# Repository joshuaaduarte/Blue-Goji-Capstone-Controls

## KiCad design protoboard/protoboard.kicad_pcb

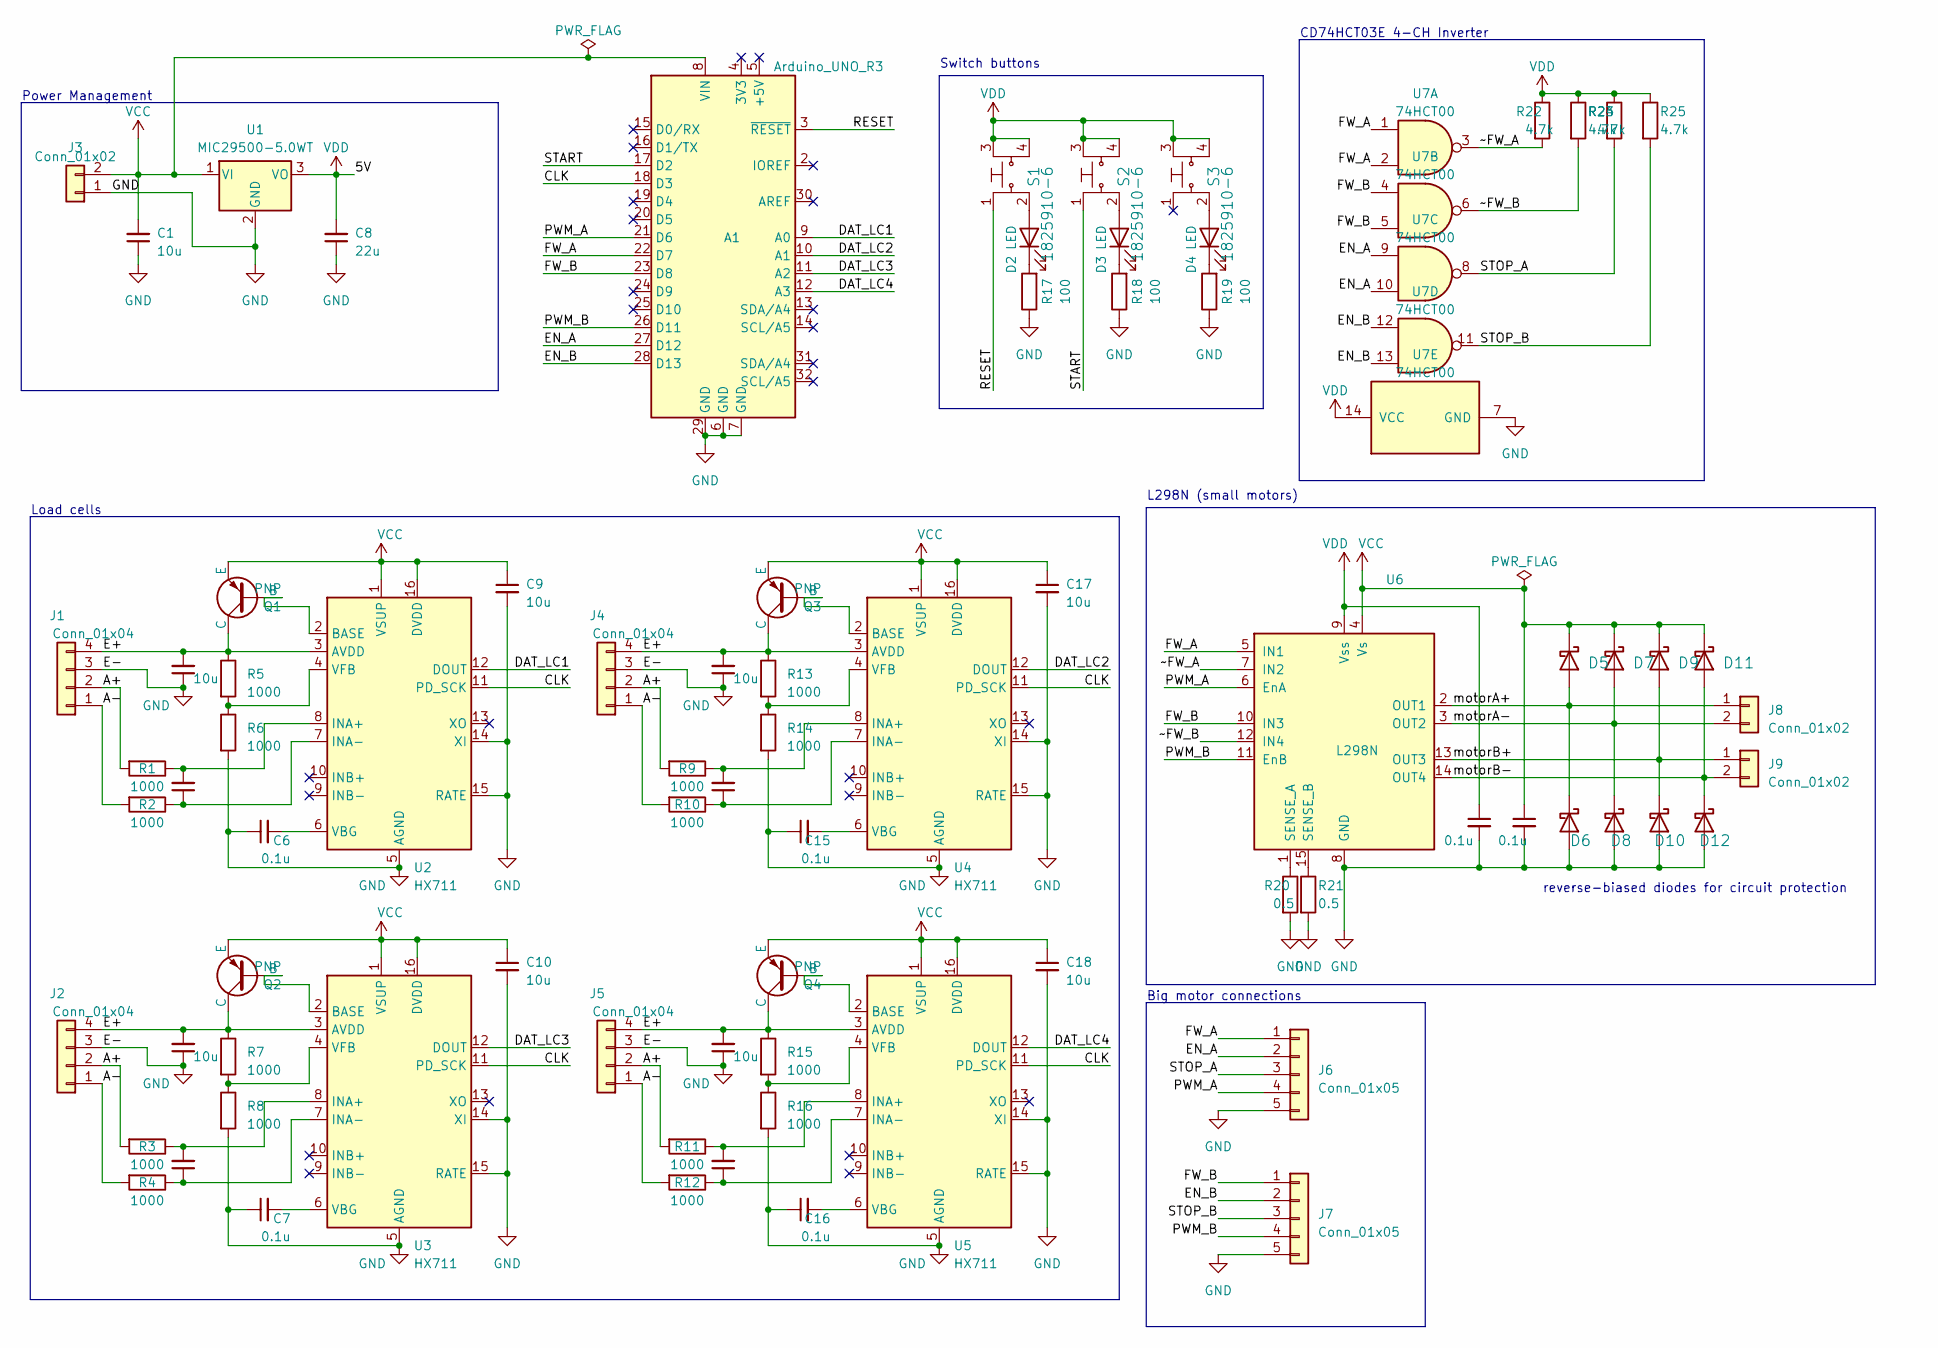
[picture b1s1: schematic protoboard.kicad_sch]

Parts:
A1: Arduino_UNO_R3
C1: 10u; CP_Radial_Tantal_D5.5mm_P2.50mm
C2, C4, C9, C10, C11, C13, C17, C18: 10u; CP_Radial_D5.0mm_P2.50mm
C3, C5, C6, C7, C12, C14, C15, C16: 0.1u; CP_Radial_D5.0mm_P2.50mm
C8: 22u; CP_Radial_Tantal_D5.5mm_P2.50mm
C19, C20: 0.1u; CP_Radial_Tantal_D5.5mm_P2.50mm
D2, D3, D4: LED; LED_D1.8mm_W1.8mm_H2.4mm_Horizontal_O1.27mm_Z1.6mm
D5, D6, D7, D8, D9, D10, D11, D12: 1N5820-TP; D_DO-201AD_P15.24mm_Horizontal; MPN 1N4001-TP; Digi-Key_PN 1N4001-TPMSCT-ND
J1, J2, J4, J5: Conn_01x04; TerminalBlock_bornier-4_P5.08mm
J3, J8, J9: Conn_01x02; TerminalBlock_TE_282834-2_1x02_P2.54mm_Horizontal
J6, J7: Conn_01x05; TerminalBlock_bornier-5_P5.08mm
Q1, Q2, Q3, Q4: PNP; TO-92
R1, R2, R3, R4, R5, R6, R7, R8, R9, R10, R11, R12, R13, R14, R15, R16: 1000; R_Axial_DIN0204_L3.6mm_D1.6mm_P2.54mm_Vertical
R17, R18, R19: 100; R_Axial_DIN0204_L3.6mm_D1.6mm_P2.54mm_Vertical
R20, R21: 0.5; R_Axial_DIN0204_L3.6mm_D1.6mm_P2.54mm_Vertical
R22, R23, R24, R25: 4.7k; R_Axial_DIN0204_L3.6mm_D1.6mm_P2.54mm_Vertical
S1, S2, S3: 1825910-6; Switch_Tactile_THT_6x6mm; MPN 1825910-6; Digi-Key_PN 450-1650-ND
U1: MIC29500-5.0WT; TO-220-3
U2, U3, U4, U5: HX711; SOP-16_3.9x9.9mm_P1.27mm
U6: L298N; TO-220-15_P2.54x2.54mm_StaggerOdd_Lead4.58mm_Vertical
U7: 74HCT00; DIP-14_W7.62mm

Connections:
/A+: J1.2, J2.2, J4.2, J5.2, R1.2, R3.2, R9.2, R11.2
/A-: J1.1, J2.1, J4.1, J5.1, R2.2, R4.2, R10.2, R12.2
/CLK: A1.18 (D3), U2.11 (PD_SCK), U3.11 (PD_SCK), U4.11 (PD_SCK), U5.11 (PD_SCK)
/DAT_LC1: A1.9 (A0), U2.12 (DOUT)
/DAT_LC2: A1.10 (A1), U4.12 (DOUT)
/DAT_LC3: A1.11 (A2), U3.12 (DOUT)
/DAT_LC4: A1.12 (A3), U5.12 (DOUT)
/E+: C2.2, C4.2, C11.2, C13.2, J1.4, J2.4, J4.4, J5.4, Q1.1 (C), Q2.1 (C), Q3.1 (C), Q4.1 (C), R5.1, R7.1, R13.1, R15.1, U2.3 (AVDD), U3.3 (AVDD), U4.3 (AVDD), U5.3 (AVDD)
/EN_A: A1.27 (D12), J6.2, U7.9, U7.10
/EN_B: A1.28 (D13), J7.2, U7.12, U7.13
/FW_A: A1.22 (D7), J6.1, U6.5 (IN1), U7.1, U7.2
/FW_B: A1.23 (D8), J7.1, U6.10 (IN3), U7.4, U7.5
/PWM_A: A1.21 (D6), J6.4, U6.6 (EnA)
/PWM_B: A1.26 (D11), J7.4, U6.11 (EnB)
/RESET: A1.3 (~RESET), S1.1
/START: A1.17 (D2), S2.1
/STOP_A: J6.3, R24.2, U7.8
/STOP_B: J7.3, R25.2, U7.11
/motorA+: D5.2 (A), D6.1 (K), J8.1, U6.2 (OUT1)
/motorA-: D7.2 (A), D8.1 (K), J8.2, U6.3 (OUT2)
/motorB+: D9.2 (A), D10.1 (K), J9.1, U6.13 (OUT3)
/motorB-: D11.2 (A), D12.1 (K), J9.2, U6.14 (OUT4)
/~FW_A: R22.2, U6.7 (IN2), U7.3
/~FW_B: R23.2, U6.12 (IN4), U7.6
GND: A1.6 (GND), A1.7 (GND), A1.29 (GND), C1.1, C2.1, C4.1, C6.1, C7.1, C8.1, C9.2, C10.2, C11.1, C13.1, C15.1, C16.1, C17.2, C18.2, C19.2, C20.2, D6.2 (A), D8.2 (A), D10.2 (A), D12.2 (A), J1.3, J2.3, J3.1, J4.3, J5.3, J6.5, J7.5, R6.2, R8.2, R14.2, R16.2, R17.1, R18.1, R19.1, R20.2, R21.2, U1.2 (GND), U2.5 (AGND), U2.14 (XI), U2.15 (RATE), U3.5 (AGND), U3.14 (XI), U3.15 (RATE), U4.5 (AGND), U4.14 (XI), U4.15 (RATE), U5.5 (AGND), U5.14 (XI), U5.15 (RATE), U6.8 (GND), U7.7 (GND)
unnamed: D2.2 (A), S1.2
unnamed: D2.1 (K), R17.2
unnamed: D3.2 (A), S2.2
unnamed: D3.1 (K), R18.2
unnamed: D4.2 (A), S3.2
unnamed: D4.1 (K), R19.2
unnamed: Q1.2 (B), U2.2 (BASE)
unnamed: Q2.2 (B), U3.2 (BASE)
unnamed: Q3.2 (B), U4.2 (BASE)
unnamed: Q4.2 (B), U5.2 (BASE)
unnamed: C3.2, R1.1, U2.8 (INA+)
unnamed: C3.1, R2.1, U2.7 (INA-)
unnamed: C6.2, U2.6 (VBG)
unnamed: R5.2, R6.1, U2.4 (VFB)
unnamed: C5.2, R3.1, U3.8 (INA+)
unnamed: C5.1, R4.1, U3.7 (INA-)
unnamed: C7.2, U3.6 (VBG)
unnamed: R7.2, R8.1, U3.4 (VFB)
unnamed: C12.2, R9.1, U4.8 (INA+)
unnamed: C12.1, R10.1, U4.7 (INA-)
unnamed: C15.2, U4.6 (VBG)
unnamed: R13.2, R14.1, U4.4 (VFB)
unnamed: C14.2, R11.1, U5.8 (INA+)
unnamed: C14.1, R12.1, U5.7 (INA-)
unnamed: C16.2, U5.6 (VBG)
unnamed: R15.2, R16.1, U5.4 (VFB)
unnamed: R20.1, U6.1 (SENSE_A)
unnamed: R21.1, U6.15 (SENSE_B)
VCC: A1.8 (VIN), C1.2, C9.1, C10.1, C17.1, C18.1, C20.1, D5.1 (K), D7.1 (K), D9.1 (K), D11.1 (K), J3.2, Q1.3 (E), Q2.3 (E), Q3.3 (E), Q4.3 (E), U1.1 (VI), U2.1 (VSUP), U2.16 (DVDD), U3.1 (VSUP), U3.16 (DVDD), U4.1 (VSUP), U4.16 (DVDD), U5.1 (VSUP), U5.16 (DVDD), U6.4 (Vs)
VDD: C8.2, C19.1, R22.1, R23.1, R24.1, R25.1, S1.3, S1.4, S2.3, S2.4, S3.3, S3.4, U1.3 (VO), U6.9 (Vss), U7.14 (VCC)

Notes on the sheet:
CD74HCT03E 4-CH Inverter
Switch buttons
Load cells
reverse-biased diodes for circuit protection
L298N (small motors)
Power Management
Big motor connections

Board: 2 copper layers, 80 parts (0 on the bottom side), 55 nets, no tracks yet.

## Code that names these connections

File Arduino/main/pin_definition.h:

/*
 * Blue Goji Omnidirectional Treadmill Capstone
 * University of California Berkeley MEng 2023
 * Author: Billy Lin 
 * Last-Edit: 02-14-2023
 */

#ifndef PIN_DEFINITION_H
#define PIN_DEFINITION_H

// motor pin definitions
#define pwmA 6
#define pwmB 11
#define fwA 7 // equivalent to in1A, in2A is obtained by negating this signal
#define fwB 8
#define enA 12 // only used in big motors
#define enB 13

// Pin definitions for load cells
#define clk 3
#define dat_lc1 14
#define dat_lc2 15
#define dat_lc3 16
#define dat_lc4 17

#define startButton 2  // Green
#define emergencyButton 4 // Yellow

#endif

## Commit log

2022-12-07 Initial commit with pose function
2023-01-20 Updated script to include center point on hip and arrow that will change with direction
2023-01-21 Added arrow that is dependent on the direction user is facing
2023-01-22 updated script for directional arrow
2023-01-23 adjusted script to allow user to rotate 360 degrees and be followed respectively by created arrow
2023-01-23 Updated py file to contain script for capturing user position and projecting that to an arrow that can be displayed to the user.
2023-02-02 first commit of software submodules
2023-02-03 Updated positioning script.
2023-02-09 updated relay logic so power stays on during idle
2023-02-09 added calculation formula in the comment for reference
2023-02-09 first working motor driver interfacing with timer interrupts
2023-02-10 completed motor driver and set up multiple data parsing from serial
2023-02-10 added two directional motor driver control
2023-02-16 working main code and edited motor driver
2023-03-16 working main code with load cell
2023-04-03 Slight change
2023-04-04 added pid test code
2023-05-03 added completed pcb schematics, finalized board pin numbers
